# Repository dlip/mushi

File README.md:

# Mushi Keyboard

Mushi (Japanese for bug) is a simple 36 key split ergonomic keyboard.

## Features

- Uses 2 cheap RP2040-Zero MCU
- Low profile Choc switches
- Hot swappable (optional)
- Requires no diodes
- Inner thumb splay to make it easier to reach
- Created with [Ergogen](https://github.com/ergogen/ergogen) and [KiCad](https://www.kicad.org)

## Build Your Own

### Board

#### Parts

- Send the [Gerber](kicad/gerber_to_order) file to the PCB manufacturer of your choice
- 2 x RP2040-Zero
- 2 x TRRS socket
- 1 x TRRS cable
- 36 x low profile choc switches and keycaps
- (optional) 36 x kailh hotswap sockets
- (optional) RP2040-Zero headers

#### Instructions

- Solder the RP2040-Zeros to the board either directly or using the headers you purchased
- Build and flash the firmware
- [QMK](https://github.com/dlip/qmk_firmware/tree/dlip/keyboards/mushi)

Left side

```
qmk flash -kb mushi -km default -bl uf2-split-left
```

Right side

```
qmk flash -kb mushi -km default -bl uf2-split-right
```

- You can test the boards at this point by connecting the hotswap pads with some metal tweezers before continuing
- Solder the kalih hotswap sockets if purchased or solder the switches directly the board otherwise
- Solder the TRRS sockets to the board
- Insert the switches into the hotswap sockets if necessary
- Add your keycaps
- Connect TRRS cable before connecting the usb cable and remember to disconnect it after disconnecting the usb cable
- Create your own keymap by forking my repo and either modifying the default keymap or copying it to a new name and changing 'default' in the flash command

### Case

#### Parts

- 3D print the left and right cases in the [case](case/) folder
- 8 x Knurled Insert Nuts (M2 x 3mm Length x 3.2mm OD) [example](https://www.amazon.com/dp/B07LBQFNQD)
- 8 x M2 3mm flat screws [example](https://www.amazon.com/gp/product/B01FTI8TM8/)
- 10-16 x Rubber feet

#### Instructions

- Use a soldering iron to melt the insert nuts into the holes in the cases
- Screw the boards to the cases
- Stick rubber feet to bottom

### Credits

- alinelena for checking my work and helping me make such beautiful tracks
- logturnal for the cool [bug logo](https://www.freepik.com/free-vector/ladybug-simple-mascot-logo-design-illustration_57161077.htm)

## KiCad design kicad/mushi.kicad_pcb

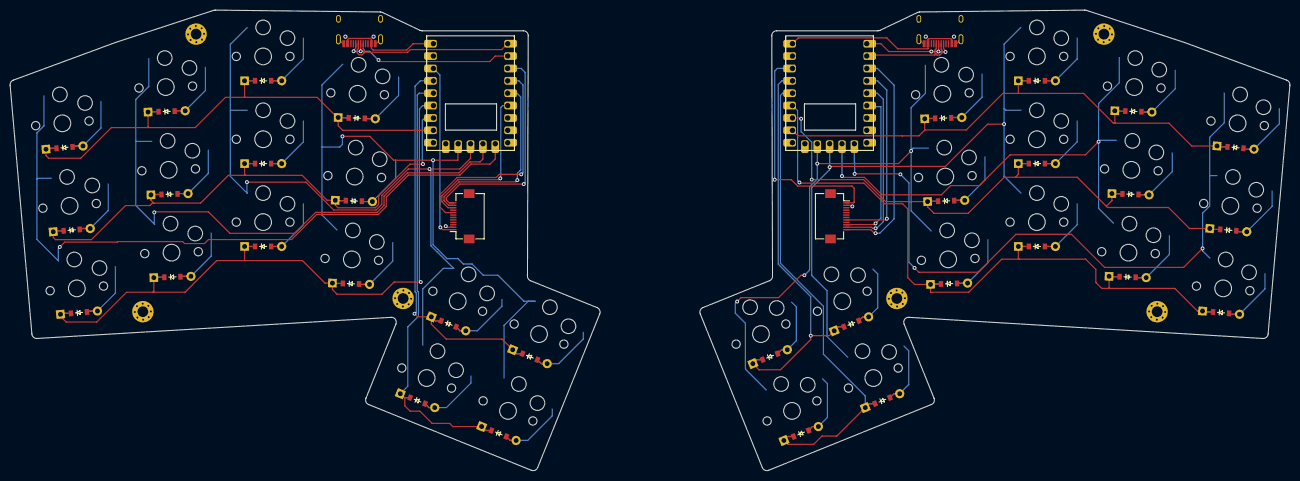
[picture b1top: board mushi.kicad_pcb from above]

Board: 2 copper layers, 262.6 x 94.5 mm, 72 parts (0 on the bottom side), 50 nets.

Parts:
D1, D2, D3, D4, D5, D6, D7, D8, D9, D10, D11, D12, D13, D14, D15, D16, D17, D18, D19, D20, D21, D22, D23, D24, D25, D26, D27, D28, D29, D30, D31, D32: ComboDiode
RP2040Zero1, RP2040Zero2: RP2040-Zero
S1, S2, S3, S4, S5, S6, S7, S8, S9, S10, S11, S12, S13, S14, S15, S16, S17, S18, S19, S20, S21, S22, S23, S24, S25, S26, S27, S28, S29, S30, S31, S32: PG1350
_1, _2, _3, _4, _5, _6: MountingHole_2.2mm_M2_Pad_Via

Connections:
index_bottom: D10.2, S10.2
index_middle: D11.2, S11.2
index_top: D12.2, S12.2
inner_bottom: D13.2, S13.2
inner_top: D14.2, S14.2
lGP9: RP2040Zero1.10, S1.1, S2.1, S3.1
lGP10: RP2040Zero1.11, S4.1, S5.1, S6.1
lGP11: RP2040Zero1.12, S7.1, S8.1, S9.1, S13.1, S14.1
lGP12: RP2040Zero1.13, S10.1, S11.1, S12.1, S15.1, S16.1
lGP15: D3.1, D6.1, D9.1, D12.1, RP2040Zero1.16
lGP26: D2.1, D5.1, D8.1, D11.1, RP2040Zero1.17
lGP27: D1.1, D4.1, D7.1, D10.1, RP2040Zero1.18
lGP28: D13.1, D15.1, RP2040Zero1.22
lGP29: D14.1, D16.1, RP2040Zero1.23
middle_bottom: D7.2, S7.2
middle_middle: D8.2, S8.2
middle_top: D9.2, S9.2
mirror_index_bottom: D26.2, S26.2
mirror_index_middle: D27.2, S27.2
mirror_index_top: D28.2, S28.2
mirror_inner_bottom: D29.2, S29.2
mirror_inner_top: D30.2, S30.2
mirror_middle_bottom: D23.2, S23.2
mirror_middle_middle: D24.2, S24.2
mirror_middle_top: D25.2, S25.2
mirror_outer_bottom: D31.2, S31.2
mirror_outer_top: D32.2, S32.2
mirror_pinky_bottom: D17.2, S17.2
mirror_pinky_middle: D18.2, S18.2
mirror_pinky_top: D19.2, S19.2
mirror_ring_bottom: D20.2, S20.2
mirror_ring_middle: D21.2, S21.2
mirror_ring_top: D22.2, S22.2
outer_bottom: D15.2, S15.2
outer_top: D16.2, S16.2
pinky_bottom: D1.2, S1.2
pinky_middle: D2.2, S2.2
pinky_top: D3.2, S3.2
rGP9: RP2040Zero2.10, S17.1, S18.1, S19.1
rGP10: RP2040Zero2.11, S20.1, S21.1, S22.1
rGP11: RP2040Zero2.12, S23.1, S24.1, S25.1, S29.1, S30.1
rGP12: RP2040Zero2.13, S26.1, S27.1, S28.1, S31.1, S32.1
rGP15: D19.1, D22.1, D25.1, D28.1, RP2040Zero2.16
rGP26: D18.1, D21.1, D24.1, D27.1, RP2040Zero2.17
rGP27: D17.1, D20.1, D23.1, D26.1, RP2040Zero2.18
rGP28: D29.1, D31.1, RP2040Zero2.22
rGP29: D30.1, D32.1, RP2040Zero2.23
ring_bottom: D4.2, S4.2
ring_middle: D5.2, S5.2
ring_top: D6.2, S6.2

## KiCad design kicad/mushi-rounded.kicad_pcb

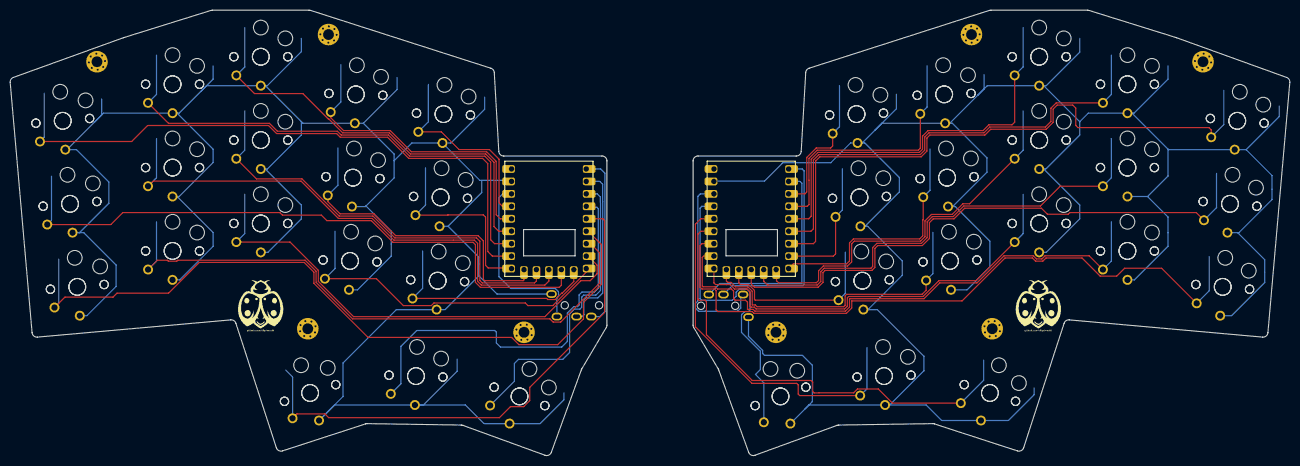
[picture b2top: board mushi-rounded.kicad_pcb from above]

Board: 2 copper layers, 261.0 x 90.8 mm, 84 parts (0 on the bottom side), 44 nets.

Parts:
RP2040Zero1, RP2040Zero2: RP2040-Zero
S1, S2, S3, S4, S5, S6, S7, S8, S9, S10, S11, S12, S13, S14, S15, S16, S17, S18, S19, S20, S21, S22, S23, S24, S25, S26, S27, S28, S29, S30, S31, S32, S33, S34, S35, S36, S37, S38, S39, S40, S41, S42, S43, S44, S45, S46, S47, S48, S49, S50, S51, S52, S53, S54, S55, S56, S57, S58, S59, S60, S61, S62, S63, S64, S65, S66, S67, S68, S69, S70, S71, S72: PG1350
TRRS1, TRRS2: TRRS-PJ-320A-dual
_1, _2, _3, _4, _5, _6, _7, _8: MountingHole_2.2mm_M2_Pad_Via

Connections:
GND: RP2040Zero1.20, S1.2, S2.2, S3.2, S4.2, S5.2, S6.2, S7.2, S8.2, S9.2, S10.2, S11.2, S12.2, S13.2, S14.2, S15.2, S16.2, S17.2, S18.2, S19.2, S20.2, S21.2, S22.2, S23.2, S24.2, S25.2, S26.2, S27.2, S28.2, S29.2, S30.2, S31.2, S32.2, S33.2, S34.2, S35.2, S36.2, TRRS1.1
P3V3: RP2040Zero1.21, TRRS1.2
RX: RP2040Zero1.2, TRRS1.3
TX: RP2040Zero1.1, TRRS1.4
matrix_index_bottom: RP2040Zero1.9, S10.1, S28.1
matrix_index_middle: RP2040Zero1.14, S11.1, S29.1
matrix_index_top: RP2040Zero1.22, S12.1, S30.1
matrix_middle_bottom: RP2040Zero1.8, S7.1, S25.1
matrix_middle_middle: RP2040Zero1.13, S8.1, S26.1
matrix_middle_top: RP2040Zero1.18, S9.1, S27.1
matrix_outer_bottom: RP2040Zero1.10, S13.1, S31.1
matrix_outer_middle: RP2040Zero1.15, S14.1, S32.1
matrix_outer_top: RP2040Zero1.23, S15.1, S33.1
matrix_pinky_bottom: RP2040Zero1.6, S1.1, S19.1
matrix_pinky_middle: RP2040Zero1.11, S2.1, S20.1
matrix_pinky_top: RP2040Zero1.16, S3.1, S21.1
matrix_ring_bottom: RP2040Zero1.7, S4.1, S22.1
matrix_ring_middle: RP2040Zero1.12, S5.1, S23.1
matrix_ring_top: RP2040Zero1.17, S6.1, S24.1
mirror_matrix_index_bottom: RP2040Zero2.14, S46.1, S64.1
mirror_matrix_index_middle: RP2040Zero2.9, S47.1, S65.1
mirror_matrix_index_top: RP2040Zero2.4, S48.1, S66.1
mirror_matrix_middle_bottom: RP2040Zero2.15, S43.1, S61.1
mirror_matrix_middle_middle: RP2040Zero2.10, S44.1, S62.1
mirror_matrix_middle_top: RP2040Zero2.5, S45.1, S63.1
mirror_matrix_outer_bottom: RP2040Zero2.13, S49.1, S67.1
mirror_matrix_outer_middle: RP2040Zero2.8, S50.1, S68.1
mirror_matrix_outer_top: RP2040Zero2.3, S51.1, S69.1
mirror_matrix_pinky_bottom: RP2040Zero2.17, S37.1, S55.1
mirror_matrix_pinky_middle: RP2040Zero2.12, S38.1, S56.1
mirror_matrix_pinky_top: RP2040Zero2.7, S39.1, S57.1
mirror_matrix_ring_bottom: RP2040Zero2.16, S40.1, S58.1
mirror_matrix_ring_middle: RP2040Zero2.11, S41.1, S59.1
mirror_matrix_ring_top: RP2040Zero2.6, S42.1, S60.1
mirror_thumbs_inner_cluster: RP2040Zero2.18, S52.1, S70.1
mirror_thumbs_middle_cluster: RP2040Zero2.22, S53.1, S71.1
mirror_thumbs_outer_cluster: RP2040Zero2.23, S54.1, S72.1
rGND: RP2040Zero2.20, S37.2, S38.2, S39.2, S40.2, S41.2, S42.2, S43.2, S44.2, S45.2, S46.2, S47.2, S48.2, S49.2, S50.2, S51.2, S52.2, S53.2, S54.2, S55.2, S56.2, S57.2, S58.2, S59.2, S60.2, S61.2, S62.2, S63.2, S64.2, S65.2, S66.2, S67.2, S68.2, S69.2, S70.2, S71.2, S72.2, TRRS2.1
rP3V3: RP2040Zero2.21, TRRS2.2
rRX: RP2040Zero2.2, TRRS2.4
rTX: RP2040Zero2.1, TRRS2.3
thumbs_inner_cluster: RP2040Zero1.5, S16.1, S34.1
thumbs_middle_cluster: RP2040Zero1.4, S17.1, S35.1
thumbs_outer_cluster: RP2040Zero1.3, S18.1, S36.1

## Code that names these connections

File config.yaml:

units:
  # Proxy Spacing Variables
  kx: cx
  ky: cy
  # Padding Variables
  px: kx + 2
  py: ky + 2
  # Double Padding Variables
  dpx: kx + 8
  dpy: ky + 8
  # M2 Screw Inserts
  screwRadius: 1.50
  standoffRadius: 3
  # Footprints
  rp2040zero_x: 18
  rp2040zero_y: 23.5
  usb_x: 8.94
  usb_y: 7.35
  fpc_x: 5
  fpc_y: 11
points:
  zones:
    matrix:
      anchor:
        shift: [30, -80]
      key:
        padding: 1ky
        spread: 1kx
      columns:
        pinky:
          key:
            splay: 5
            column_net: lGP9
            mirror.column_net: rGP9
        ring:
          key:
            stagger: 0.33ky
            splay: -3
            spread: 1kx + 2
            column_net: lGP10
            mirror.column_net: rGP10
        middle:
          key:
            stagger: 0.33ky
            splay: -2
            spread: 1kx + 1
            column_net: lGP11
            mirror.column_net: rGP11
        index:
          key:
            stagger: -0.45ky
            splay: -2
            spread: 1kx + 0.2
            column_net: lGP12
            mirror.column_net: rGP12
      rows:
        bottom:
          row_net: lGP27
          mirror.row_net: rGP27
        middle:
          row_net: lGP26
          mirror.row_net: rGP26
        top:
          row_net: lGP15
          mirror.row_net: rGP15
    thumbs:
      key:
        padding: 1ky
        spread: 1kx
      anchor:
        ref: matrix_index_bottom
        shift: [.9kx, -1.2ky]
      columns:
        inner:
          key:
            width: 1.5kx
            splay: -20
            stagger: -0.2ky
            column_net: lGP11
            mirror.column_net: rGP11
        outer:
          key:
            width: 1.5kx
            spread: 1ky+1
            column_net: lGP12
            mirror.column_net: rGP12
      rows:
        bottom:
          row_net: lGP28
          mirror.row_net: rGP28
        top:
          row_net: lGP29
          mirror.row_net: rGP29
    mcu:
      anchor:
        ref: matrix_middle_top
        shift: [2.3kx, -.5ky]
      key:
        width: rp2040zero_x
        height: rp2040zero_y
    cirque:
      anchor:
        ref: mcu
        shift: [.5kx, -1.5ky]
      key:
        width: rp2040zero_x
        height: rp2040zero_y
    fpc:
      anchor:
        ref: mcu
        shift: [0.5kx, -1.5ky]
      key:
        width: fpc_x
        height: fpc_y
    usb:
      anchor:
        ref: matrix_middle_top
        shift: [1.1kx, .32ky]
      key:
        width: usb_x
        height: usb_y
    holeRingTop:
      anchor:
        ref: [matrix_ring_top]
        shift: [0.33px, 0.56py]
    holeRingBottom:
      anchor:
        ref: [matrix_ring_bottom]
        shift: [-0.35kx, -0.7ky]
    holeOuterThumbs:
      anchor:
        ref: [matrix_index_bottom]
        shift: [0.6kx, -0.45ky]
  mirror: &mirror
    ref: matrix_index_top
    distance: 120
outlines:
  keys:
    - what: rectangle
      where: /matrix|thumb/
      size: [kx-0.5, ky-0.5]
  boardLeft:
    - what: polygon
      operation: stack
      fillet: 1
      points:
        - ref: matrix_pinky_top
          shift: [-0.5px, 0.5py]
        - ref: matrix_ring_top
          shift: [-0.5px, 0.5py]
        - ref: matrix_middle_top
          shift: [-0.5px, 0.5py]
        - ref: usb
          shift: [usb_x/2, usb_y/2]
        - ref: mcu
          shift: [-rp2040zero_x/2, rp2040zero_y/2+2]
        - ref: mcu
          shift: [rp2040zero_x/2+4, rp2040zero_y/2+2]
        - ref: thumbs_outer_top
          shift: [-0.32px, 0.5py]
        - ref: thumbs_outer_top
          shift: [0.5px, 0.5py]
        - ref: thumbs_outer_bottom
          shift: [0.5px, 0.5py]
        - ref: thumbs_outer_bottom
          shift: [0.5px, -0.5py]
        - ref: thumbs_inner_bottom
          shift: [-0.5px, -0.5py]
        - ref: thumbs_inner_bottom
          shift: [-0.5px, 0.5py]
        - ref: matrix_pinky_bottom
          shift: [-0.5px, -0.5py]
  boardRight:
    - what: polygon
      operation: stack
      fillet: 1
      points:
        - ref: mirror_matrix_pinky_top
          shift: [-0.5px, 0.5py]
        - ref: mirror_matrix_ring_top
          shift: [-0.5px, 0.5py]
        - ref: mirror_matrix_middle_top
          shift: [-0.5px, 0.5py]
        - ref: mirror_usb
          shift: [usb_x/2, usb_y/2]
        - ref: mirror_mcu
          shift: [-rp2040zero_x/2, rp2040zero_y/2+2]
        - ref: mirror_mcu
          shift: [rp2040zero_x/2+4, rp2040zero_y/2+2]
        - ref: mirror_thumbs_outer_top
          shift: [-0.32px, 0.5py]
        - ref: mirror_thumbs_outer_top
          shift: [0.5px, 0.5py]
        - ref: mirror_thumbs_outer_bottom
          shift: [0.5px, 0.5py]
        - ref: mirror_thumbs_outer_bottom
          shift: [0.5px, -0.5py]
        - ref: mirror_thumbs_inner_bottom
          shift: [-0.5px, -0.5py]
        - ref: mirror_thumbs_inner_bottom
          shift: [-0.5px, 0.5py]
        - ref: mirror_matrix_pinky_bottom
          shift: [-0.5px, -0.5py]
  board:
    - boardLeft
    - boardRight
  _mcu:
    - what: rectangle
      where: /mcu/
      size: [rp2040zero_x, rp2040zero_y]
  _fpc:
    - what: rectangle
      where: /fpc/
      size: [fpc_x, fpc_y]
  _cirque:
    - what: circle
      where: /cirque/
      radius: 20
  _usb:
    - what: rectangle
      where: /usb/
      size: [usb_x, usb_y]
  _mountingLeft:
    - what: circle
      where: /^hole/
      radius: screwRadius
  _mountingRight:
    - what: circle
      where: /^mirror_hole/
      radius: screwRadius
  _standoffLeft:
    - what: circle
      where: /^hole/
      radius: standoffRadius
  _standoffRight:
    - what: circle
      where: /^hole/
      radius: standoffRadius
  combo:
    - ^boardLeft
    - ^boardRight
    - ^keys
    - ^_mcu
    - ^_fpc
    - ^_cirque
    - ^_usb
    - ^_standoffLeft
    - ^_standoffRight
    - ^_mountingLeft
    - ^_mountingRight
pcbs:
  mushi:
    outlines:
      main:
        outline: board
    footprints:
      chocHotswapLeft:
        what: choc
        where: /^(thumb|matrix)/
        params:
          keycaps: true
          hotswap: true
          from: "{{column_net}}"
          to: "{{colrow}}"
      diodeLeft:
        what: diode
        where: /^(thumb|matrix)/
        params:
          from: "{{colrow}}"
          to: "{{row_net}}"
        adjust:
          shift: [0, -5]
      chocHotswapRight:
        what: choc
        where: /^mirror_(thumb|matrix)/
        params:
          keycaps: true
          hotswap: true
          from: "{{mirror.column_net}}"
          to: "{{colrow}}"
      diodeRight:
        what: diode
        where: /^mirror_(thumb|matrix)/
        params:
          from: "{{colrow}}"
          to: "{{mirror.row_net}}"
        adjust:
          shift: [0, -5]
      mcuLeft:
        what: rp2040zero
        where: mcu
        adjust:
          shift: [-rp2040zero_x / 2, -rp2040zero_y / 2]
        params:
          reverse: true
          P5V: lP5V
          GND: lGND
          P3V3: lP3V3
          GP29: lGP29
          GP28: lGP28
          GP27: lGP27
          GP26: lGP26
          GP15: lGP15
          GP14: lGP14
          GP13: lGP13
          GP12: lGP12
          GP11: lGP11
          GP10: lGP10
          GP9: lGP9
          GP8: lGP8
          GP7: lGP7
          GP6: lGP6
          GP5: lGP5
          GP4: lGP4
          GP3: lGP3
          GP2: lGP2
          GP1: lGP1
          GP0: lGP0
      mcuRight:
        what: rp2040zero
        where: mirror_mcu
        adjust:
          shift: [rp2040zero_x / 2 + 2.29, -rp2040zero_y / 2]
        params:
          P5V: rP5V
          GND: rGND
          P3V3: rP3V3
          GP29: rGP29
          GP28: rGP28
          GP27: rGP27
          GP26: rGP26
          GP15: rGP15
          GP14: rGP14
          GP13: rGP13
          GP12: rGP12
          GP11: rGP11
          GP10: rGP10
          GP9: rGP9
          GP8: rGP8
          GP7: rGP7
          GP6: rGP6
          GP5: rGP5
          GP4: rGP4
          GP3: rGP3
          GP2: rGP2
          GP1: rGP1
          GP0: rGP0
      holes:
        what: mountinghole
        where: /hole/

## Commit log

2023-08-27 Add mushi
2023-08-27 round tracks
2023-08-27 separate rounded
2023-08-28 remove empty segment
2023-08-28 thinner case
2023-08-28 cleanup
2023-08-28 improve rounded
2023-08-29 smooth right side
2023-08-29 cleanup left side
2023-08-29 clean up gnd
2023-08-29 more cleanup
2023-08-29 new zones and logo
2023-08-30 update logos
2023-08-30 revert track rounding
2023-08-30 remove duplicate text
2023-08-30 Change fill to hatch pattern
2023-08-30 fix thermal relief
2023-08-30 Round tracks and export gerber
2023-08-30 add rounded again
2023-08-30 regenerate gerbers
2023-08-31 Separate left and right cases
2023-09-10 Add board
2023-09-10 add case
2023-09-12 Increase standoff depth
2023-09-12 Extend holes for case
2023-09-13 Add photo
2023-09-16 Add license
2023-10-12 Add tenting scad
2023-10-15 Add tenting case
2024-07-09 config
2024-07-09 moving
2024-07-10 move pcb back
2024-07-10 fix errors
2024-07-10 add matrix
2024-07-11 move standoffs
2024-07-11 Setup nets
2024-07-11 Fix outline
2024-07-11 add back nets
2024-07-11 wiring
2024-07-11 left side
2024-07-12 fix nets
2024-07-12 fix net
2024-07-12 route left
2024-07-12 route right
